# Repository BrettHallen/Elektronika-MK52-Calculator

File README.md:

# Elektronika MK-52 Calculator
The Электроника МК-52 (МикроКалькулятор, Micro Calculator) was an advanced Soviet programmable calculator that had 512 bytes of permanent, erasable memory (via a КР1601РР1 EEPROM) and could be expanded with additional library functions via ROM cartridges:

- РПП-1: Games & entertainment (30-40 games)
- РПП-2: Financial & economic library
- БРП-3: Mathematical library
- БРП-4: Aerospace & navigation library
- БРП-5: Engineering & construction library

РПП = Расширитель Постоянной Памяти (permanent memory expansion)<br>
БРП = Блок Расширения Памяти (memory expansion block)<br>

The БРП-4 and БРП-5 were produced in large numbers and are pretty easy to find.  The earlier ones are quite rare.

They have a pretty terrible keypad - I have attempted to design a [replacement](/Elektronika_MK52_Keypad).<br>

Thanks to Alex J. Lowry for his design files that confirmed the physical dimensions and grid for the keys.<br>

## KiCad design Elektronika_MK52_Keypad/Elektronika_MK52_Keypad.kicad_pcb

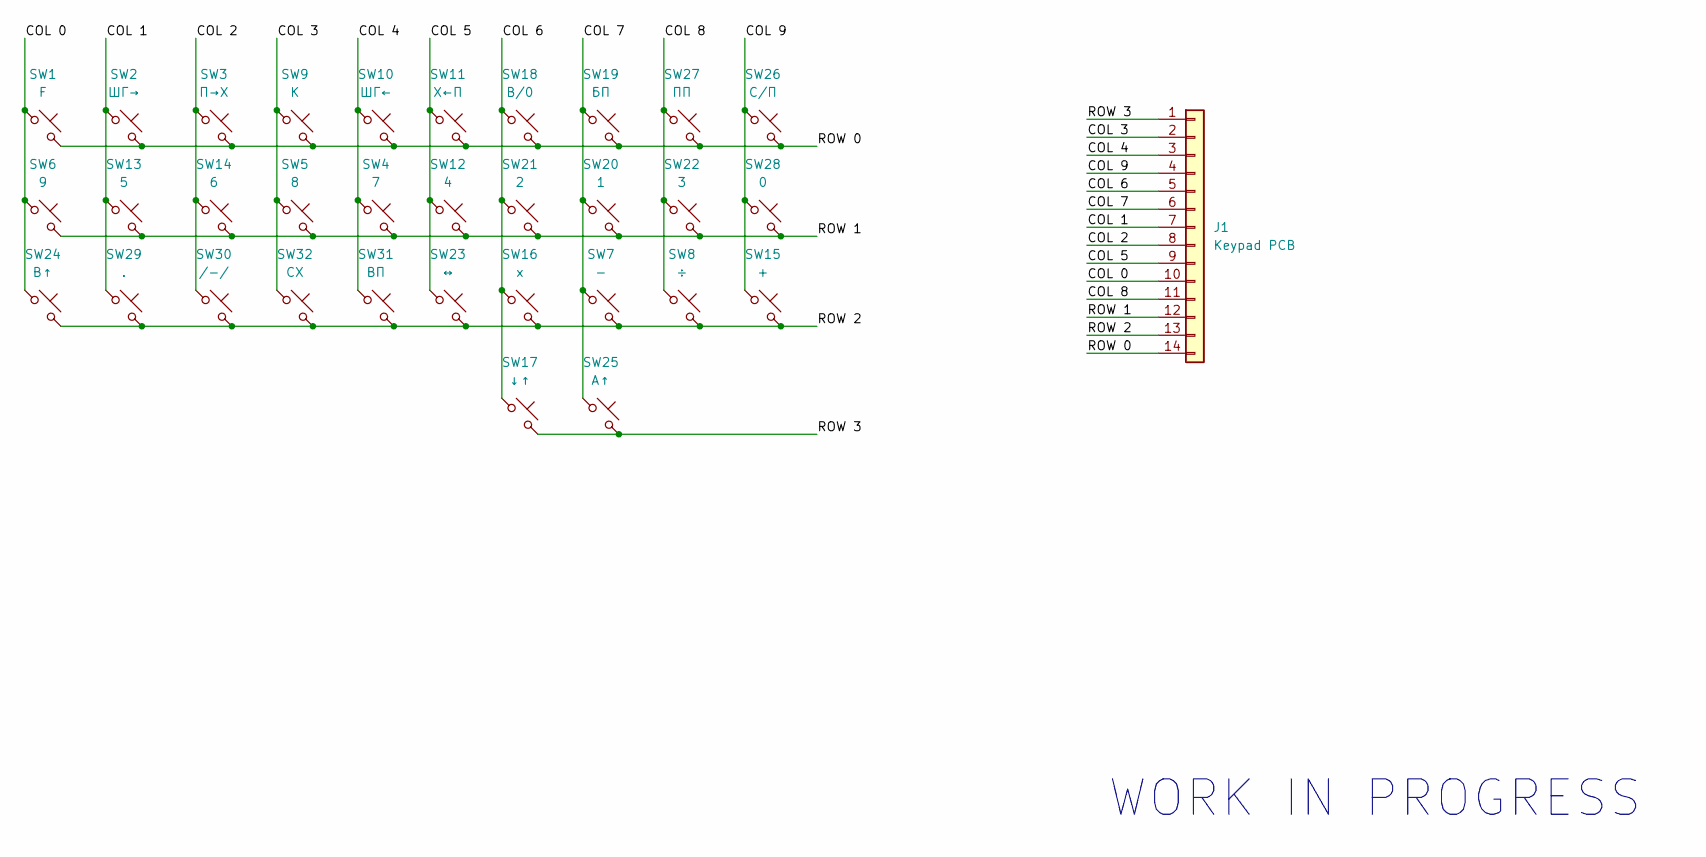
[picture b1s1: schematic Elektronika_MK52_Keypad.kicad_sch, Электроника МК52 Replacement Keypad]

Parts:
J1: Keypad PCB; PinHeader_1x14_P1.00mm_Vertical
SW1: F; MSLPT5252AL4TR
SW2: ШГ→; MSLPT5252AL4TR
SW3: П→Х; MSLPT5252AL4TR
SW4: 7; MSLPT5252AL4TR
SW5: 8; MSLPT5252AL4TR
SW6: 9; MSLPT5252AL4TR
SW7: -; MSLPT5252AL4TR
SW8: ÷; MSLPT5252AL4TR
SW9: K; MSLPT5252AL4TR
SW10: ШГ←; MSLPT5252AL4TR
SW11: Х←П; MSLPT5252AL4TR
SW12: 4; MSLPT5252AL4TR
SW13: 5; MSLPT5252AL4TR
SW14: 6; MSLPT5252AL4TR
SW15: +; MSLPT5252AL4TR
SW16: x; MSLPT5252AL4TR
SW17: ↓↑; MSLPT5252AL4TR
SW18: B/0; MSLPT5252AL4TR
SW19: БП; MSLPT5252AL4TR
SW20: 1; MSLPT5252AL4TR
SW21: 2; MSLPT5252AL4TR
SW22: 3; MSLPT5252AL4TR
SW23: ↔; MSLPT5252AL4TR
SW24: В↑; MSLPT5252AL4TR
SW25: A↑; MSLPT5252AL4TR
SW26: С/П; MSLPT5252AL4TR
SW27: ПП; MSLPT5252AL4TR
SW28: 0; MSLPT5252AL4TR
SW29: .; MSLPT5252AL4TR
SW30: /-/; MSLPT5252AL4TR
SW31: ВП; MSLPT5252AL4TR
SW32: СХ; MSLPT5252AL4TR

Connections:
/COL 0: J1.10, SW1.1, SW6.1, SW24.1
/COL 1: J1.7, SW2.1, SW13.1, SW29.1
/COL 2: J1.8, SW3.1, SW14.1, SW30.1
/COL 3: J1.2, SW5.1, SW9.1, SW32.1
/COL 4: J1.3, SW4.1, SW10.1, SW31.1
/COL 5: J1.9, SW11.1, SW12.1, SW23.1
/COL 6: J1.5, SW16.1, SW17.1, SW18.1, SW21.1
/COL 7: J1.6, SW7.1, SW19.1, SW20.1, SW25.1
/COL 8: J1.11, SW8.1, SW22.1, SW27.1
/COL 9: J1.4, SW15.1, SW26.1, SW28.1
/ROW 0: J1.14, SW1.2, SW2.2, SW3.2, SW9.2, SW10.2, SW11.2, SW18.2, SW19.2, SW26.2, SW27.2
/ROW 1: J1.12, SW4.2, SW5.2, SW6.2, SW12.2, SW13.2, SW14.2, SW20.2, SW21.2, SW22.2, SW28.2
/ROW 2: J1.13, SW7.2, SW8.2, SW15.2, SW16.2, SW23.2, SW24.2, SW29.2, SW30.2, SW31.2, SW32.2
/ROW 3: J1.1, SW17.2, SW25.2

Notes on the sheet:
WORK IN PROGRESS

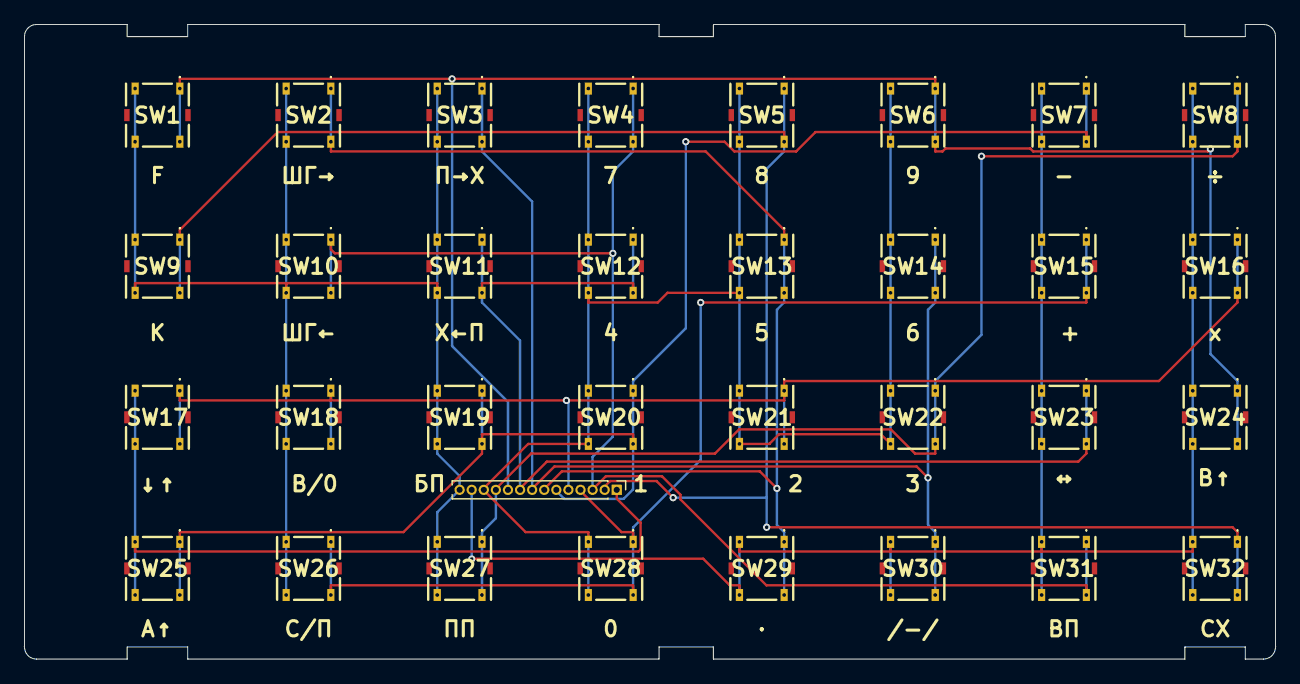
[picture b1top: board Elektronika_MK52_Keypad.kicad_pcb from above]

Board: 2 copper layers, 103.5 x 52.5 mm, 33 parts (0 on the bottom side), 14 nets.

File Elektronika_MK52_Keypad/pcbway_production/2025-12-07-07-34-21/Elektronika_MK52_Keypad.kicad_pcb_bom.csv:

Designator,Quantity,Value,Footprint,Package,MPN,DNP,Mount_Type,Description
J1,1,Keypad PCB,PinHeader_1x14_P1.00mm_Vertical,,,,tht,"Generic connector, single row, 01x14, script generated (kicad-library-utils/schlib/autogen/connector/)"
SW1,1,F,MSLPT5252AL4TR,,,,smt,"Push button switch, normally open, two pins, 45° tilted"
SW10,1,ШГ←,MSLPT5252AL4TR,,,,smt,"Push button switch, normally open, two pins, 45° tilted"
SW11,1,Х←П,MSLPT5252AL4TR,,,,smt,"Push button switch, normally open, two pins, 45° tilted"
SW12,1,4,MSLPT5252AL4TR,,,,smt,"Push button switch, normally open, two pins, 45° tilted"
SW13,1,5,MSLPT5252AL4TR,,,,smt,"Push button switch, normally open, two pins, 45° tilted"
SW14,1,6,MSLPT5252AL4TR,,,,smt,"Push button switch, normally open, two pins, 45° tilted"
SW15,1,+,MSLPT5252AL4TR,,,,smt,"Push button switch, normally open, two pins, 45° tilted"
SW16,1,x,MSLPT5252AL4TR,,,,smt,"Push button switch, normally open, two pins, 45° tilted"
SW17,1,↓↑,MSLPT5252AL4TR,,,,smt,"Push button switch, normally open, two pins, 45° tilted"
SW18,1,B/O,MSLPT5252AL4TR,,,,smt,"Push button switch, normally open, two pins, 45° tilted"
SW19,1,БП,MSLPT5252AL4TR,,,,smt,"Push button switch, normally open, two pins, 45° tilted"
SW2,1,ШГ→,MSLPT5252AL4TR,,,,smt,"Push button switch, normally open, two pins, 45° tilted"
SW20,1,1,MSLPT5252AL4TR,,,,smt,"Push button switch, normally open, two pins, 45° tilted"
SW21,1,2,MSLPT5252AL4TR,,,,smt,"Push button switch, normally open, two pins, 45° tilted"
SW22,1,3,MSLPT5252AL4TR,,,,smt,"Push button switch, normally open, two pins, 45° tilted"
SW23,1,↔,MSLPT5252AL4TR,,,,smt,"Push button switch, normally open, two pins, 45° tilted"
SW24,1,В↑,MSLPT5252AL4TR,,,,smt,"Push button switch, normally open, two pins, 45° tilted"
SW25,1,A↑,MSLPT5252AL4TR,,,,smt,"Push button switch, normally open, two pins, 45° tilted"
SW26,1,С/П,MSLPT5252AL4TR,,,,smt,"Push button switch, normally open, two pins, 45° tilted"
SW27,1,ПП,MSLPT5252AL4TR,,,,smt,"Push button switch, normally open, two pins, 45° tilted"
SW28,1,0,MSLPT5252AL4TR,,,,smt,"Push button switch, normally open, two pins, 45° tilted"
SW29,1,.,MSLPT5252AL4TR,,,,smt,"Push button switch, normally open, two pins, 45° tilted"
SW3,1,П→Х,MSLPT5252AL4TR,,,,smt,"Push button switch, normally open, two pins, 45° tilted"
SW30,1,/-/,MSLPT5252AL4TR,,,,smt,"Push button switch, normally open, two pins, 45° tilted"
SW31,1,ВП,MSLPT5252AL4TR,,,,smt,"Push button switch, normally open, two pins, 45° tilted"
SW32,1,СХ,MSLPT5252AL4TR,,,,smt,"Push button switch, normally open, two pins, 45° tilted"
SW4,1,7,MSLPT5252AL4TR,,,,smt,"Push button switch, normally open, two pins, 45° tilted"
SW5,1,8,MSLPT5252AL4TR,,,,smt,"Push button switch, normally open, two pins, 45° tilted"
SW6,1,9,MSLPT5252AL4TR,,,,smt,"Push button switch, normally open, two pins, 45° tilted"
SW7,1,-,MSLPT5252AL4TR,,,,smt,"Push button switch, normally open, two pins, 45° tilted"
SW8,1,÷,MSLPT5252AL4TR,,,,smt,"Push button switch, normally open, two pins, 45° tilted"
SW9,1,K,MSLPT5252AL4TR,,,,smt,"Push button switch, normally open, two pins, 45° tilted"

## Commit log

2025-12-06 Adjusted PCB thickness 1.6mm -> 1.0mm
2025-12-06 Created PCB outline
2025-12-06 initial PCB routing
2025-12-08 Adjusted PCB dimensions (thanks Alex!)
2025-12-08 Revised PCB layout
